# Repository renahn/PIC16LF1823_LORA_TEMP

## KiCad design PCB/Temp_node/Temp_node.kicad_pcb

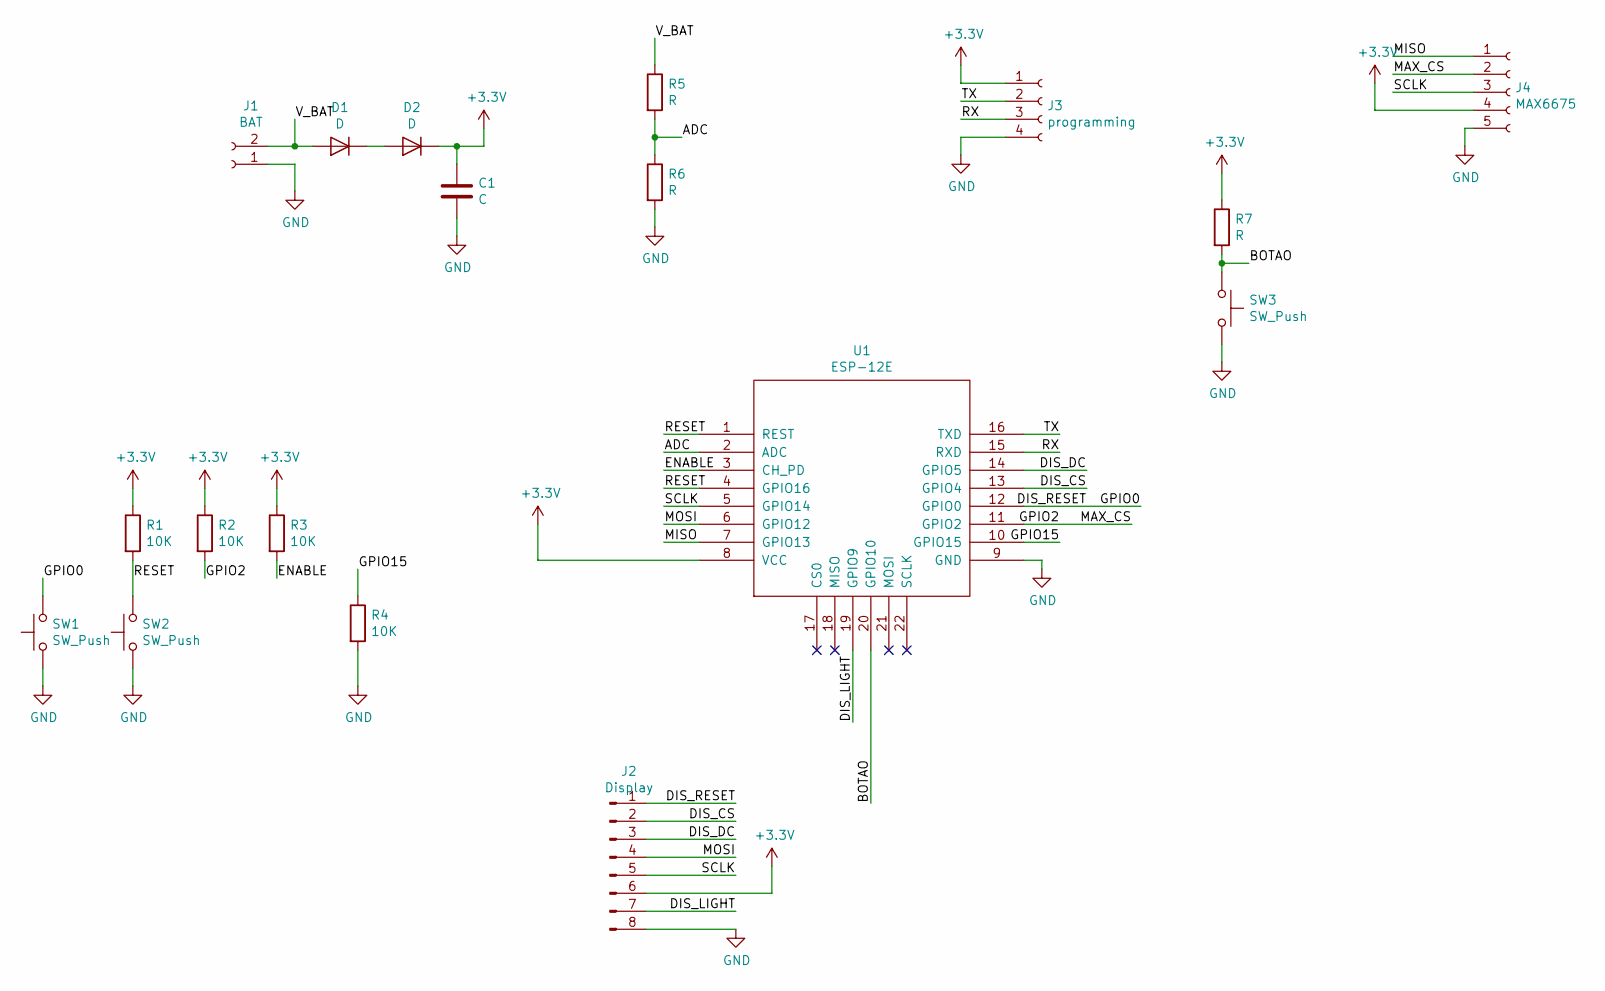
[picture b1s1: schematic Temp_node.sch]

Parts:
C1: C; CP_Radial_D8.0mm_P5.00mm
D1, D2: D; D_DO-15_P10.16mm_Horizontal
J1: BAT; PinHeader_2x01_P2.54mm_Vertical
J2: Display; PinHeader_1x08_P2.54mm_Vertical
J3: programming; PinHeader_1x04_P2.54mm_Vertical
J4: MAX6675; PinHeader_1x05_P2.54mm_Vertical
R1, R2, R3, R4: 10K; R_0805_2012Metric_Pad1.15x1.40mm_HandSolder
R5, R6, R7: R; R_0805_2012Metric_Pad1.15x1.40mm_HandSolder
SW1, SW2: SW_Push; SW_SPST_FSMSM
SW3: SW_Push; SW_SPST_TL3342
U1: ESP-12E

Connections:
+3V3: C1.1, D2.1 (K), J2.6, J3.1, J4.4, R1.1, R2.1, R3.1, R7.1, U1.8 (VCC)
/ADC: R5.2, R6.1, U1.2 (ADC)
/BOTAO: R7.2, SW3.1, U1.20 (GPIO10)
/DIS_CS: J2.2, U1.13 (GPIO4)
/DIS_DC: J2.3, U1.14 (GPIO5)
/DIS_LIGHT: J2.7, U1.19 (GPIO9)
/DIS_RESET: J2.1, SW1.2, U1.12 (GPIO0)
/ENABLE: R3.2, U1.3 (CH_PD)
/GPIO2: J4.2, R2.2, U1.11 (GPIO2)
/GPIO15: R4.1, U1.10 (GPIO15)
/MISO: J4.1, U1.7 (GPIO13)
/MOSI: J2.4, U1.6 (GPIO12)
/RESET: R1.2, SW2.2, U1.1 (REST), U1.4 (GPIO16)
/RX: J3.3, U1.15 (RXD)
/SCLK: J2.5, J4.3, U1.5 (GPIO14)
/TX: J3.2, U1.16 (TXD)
/V_BAT: D1.2 (A), J1.2, R5.1
GND: C1.2, J1.1, J2.8, J3.4, J4.5, R4.2, R6.2, SW1.1, SW2.1, SW3.2, U1.9 (GND)
unnamed: D1.1 (K), D2.2 (A)

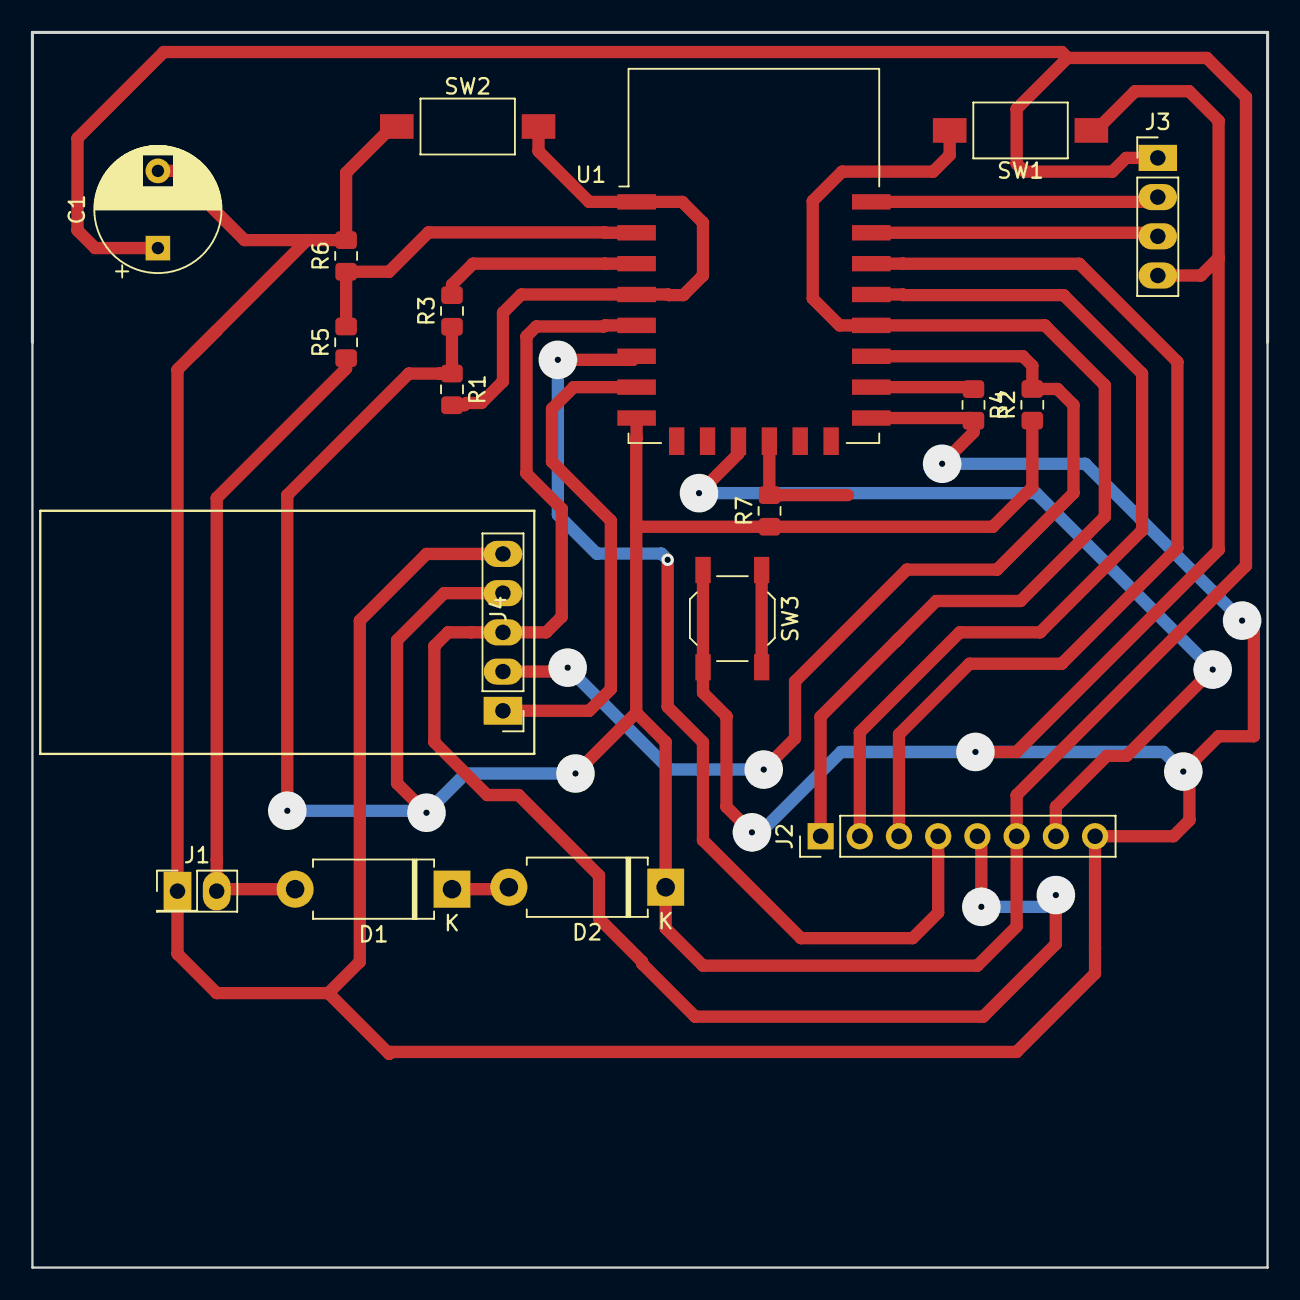
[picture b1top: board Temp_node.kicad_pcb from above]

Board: 2 copper layers, 80.0 x 80.0 mm, 18 parts (0 on the bottom side), 19 nets.

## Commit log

2019-02-20 PCB, code working
2019-02-20 enviando temperatura para o servidor e rotina de tasks criada
2019-02-21 rotina de dormir prolongada criada
2019-02-22 botao implementado
